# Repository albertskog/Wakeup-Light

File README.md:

#Raspberry Pi Wakeup-Light
This is the readme.

#MQTT API
###lights/r
A single integer value from 0 to 999 posted (as string) on this topic sets the red pulse width accordingly.

###lights/g
A single integer value from 0 to 999 posted (as string) on this topic sets the green pulse width accordingly.

###lights/b
A single integer value from 0 to 999 posted (as string) on this topic sets the blue pulse width accordingly.

###lights/rgb
A JSON object published on this topic sets all the colors at once. The key "fadeTimeMs" is optional and makes a fade from the previously set color to the new one in the time specified. Syntax:

	{
		"red":        500, 
		"green":      300, 
		"blue":       100,
		"fadeTimeMs": 1000
	}

###wakeup/state
A JSON object published on this topic sets the current state of the wakeup light sequence. Stopping the sequence while running will keep the last light setting. 

States may be one of the following:

- "start" or 1
- "stop" or 0

The parameter "wakeupTime" may optionally be passed to set the duration of the wakeup sequence.

Syntax:

	{
		"state": "start",
		"wakeupTimeMinutes": 30
	}

Alternative:

	{
		"state": 1
	}

###wakeup/time
A JSON object published on this topic sets the time it takes to perform the fading sequence. Syntax:

	{
		"wakeupTimeMinutes": 25
	}

###wakeup/alarm
A JSON object published on this topic sets the time for the wakeup sequence to start. This is an alternative to starting the sequence manually. The content will be parsed into a cronjob so comma separation can be used to add several values and "*" means "every". Syntax:

	{
		"hour":   "7", 
		"minute": "30", 
		"day": 	  "1, 2, 3, 4, 5",
		"month":  "*"
	}

#Installing

###Basics

	sudo apt-get install git screen man python-pip python-dev

###Mosquitto MQTT Broker
Get the latest version from their repository
([http://mosquitto.org/2013/01/mosquitto-debian-repository/](http://mosquitto.org/2013/01/mosquitto-debian-repository/))

```
wget http://repo.mosquitto.org/debian/mosquitto-repo.gpg.key
sudo apt-key add mosquitto-repo.gpg.key
cd /etc/apt/sources.list.d/
sudo wget http://repo.mosquitto.org/debian/mosquitto-stable.list
sudo apt-get update
sudo apt-get install mosquitto
```

###Paho MQTT Python library
([http://mosquitto.org/documentation/python/](http://mosquitto.org/documentation/python/))

	sudo pip install paho-mqtt

###Raspberry GPIO

	sudo pip install RPIO

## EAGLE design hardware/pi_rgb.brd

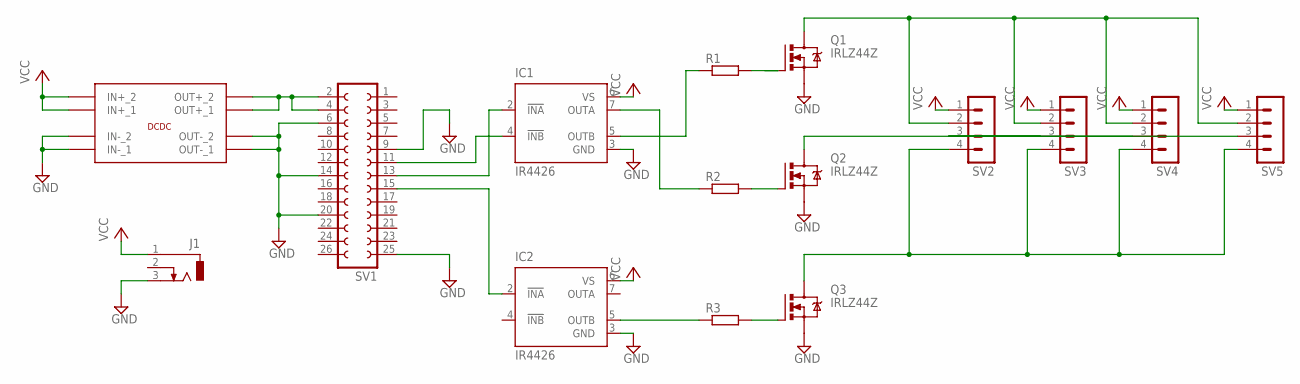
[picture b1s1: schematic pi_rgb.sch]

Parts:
5V: DCDC
IC1, IC2: IR4426; DIL08
J1: DCJ0303
Q1, Q2, Q3: IRLZ44Z; TO220BV
R1, R2, R3: R-EU_0204_5; 0204/5
SV1: FE13-2
SV2, SV3, SV4, SV5: MA04-1

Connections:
GND: 5V.IN-_1, 5V.IN-_2, 5V.OUT-_1, 5V.OUT-_2, IC1.3 (GND), IC2.3 (GND), J1.3, Q1.S, Q2.S, Q3.S, SV1.6, SV1.9, SV1.14, SV1.20, SV1.25
unnamed: IC1.4 (!INB), SV1.11
unnamed: IC1.2 (!INA), SV1.13
unnamed: IC2.2 (!INA), SV1.15
unnamed: Q2.G, R2.2
unnamed: Q3.G, R3.2
unnamed: IC2.5 (OUTB), R3.1
unnamed: Q2.D, SV2.3, SV3.3, SV4.3, SV5.3
unnamed: Q3.D, SV2.4, SV3.4, SV4.4, SV5.4
unnamed: 5V.OUT+2 (OUT+_1), 5V.OUT+_1 (OUT+_2), SV1.2, SV1.4
unnamed: Q1.G, R1.2
unnamed: Q1.D, SV2.2, SV3.2, SV4.2, SV5.2
unnamed: IC1.7 (OUTA), R2.1
unnamed: IC1.5 (OUTB), R1.1
VCC: 5V.IN+_1, 5V.IN+_2, IC1.6 (VS), IC2.6 (VS), J1.1, SV2.1, SV3.1, SV4.1, SV5.1

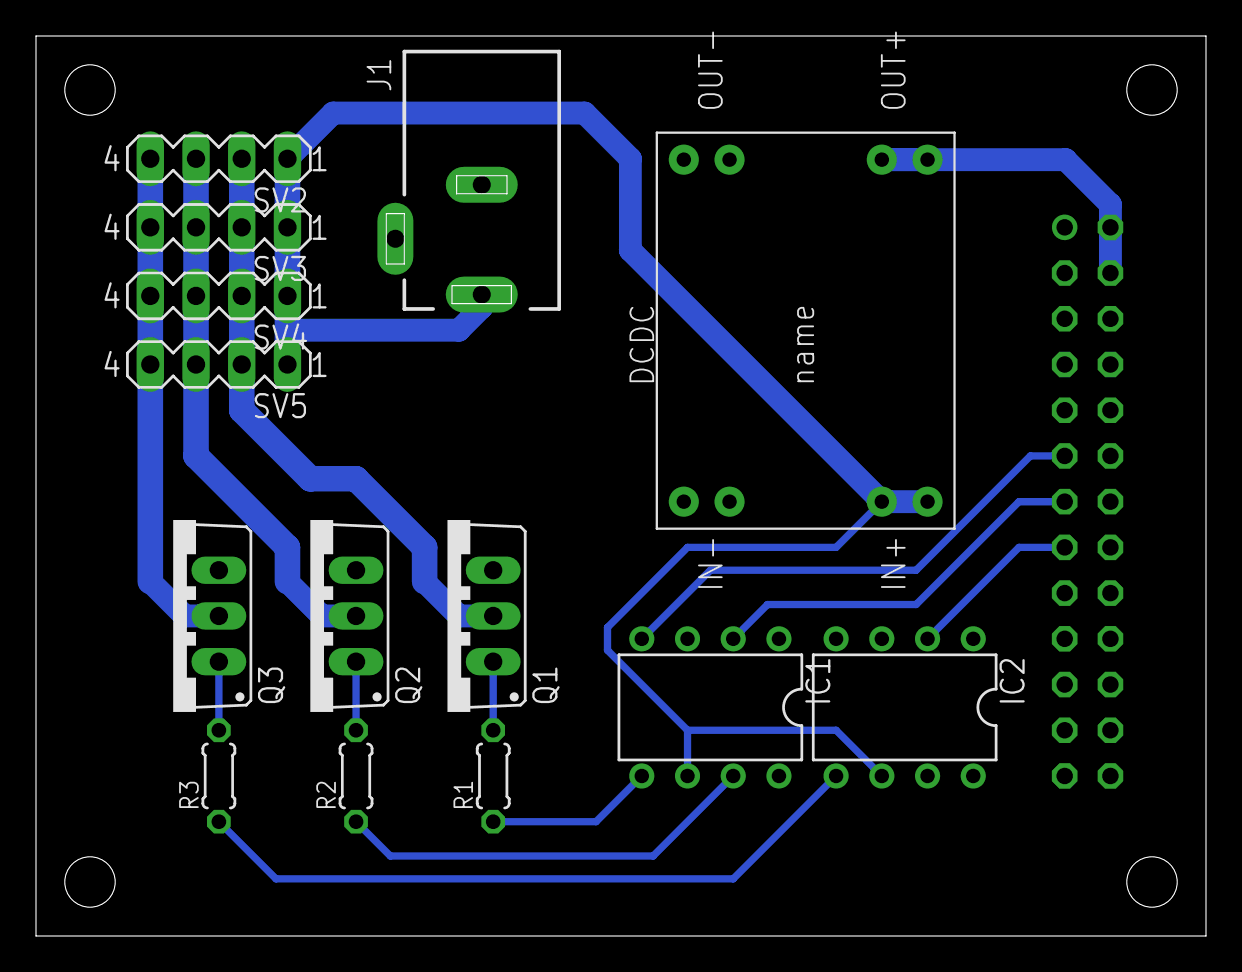
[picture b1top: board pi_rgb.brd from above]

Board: 2 copper layers, 65.0 x 50.0 mm, 15 parts (1 on the bottom side), 15 nets.

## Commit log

2014-11-16 First commit. Basic installation.
2014-11-23 Updated fade time for real test
2014-11-24 quick fixed exit crash
2014-11-25 Added simple JSON api to set all three colors at once
2014-11-26 Inital project setup
2014-11-26 moved files into /app
2014-11-26 moved .idea
2014-11-26 Updated and created a new .gitignore
2014-11-26 Updated .gitignore
2014-11-28 Started expanding wakeup API
2014-12-09 refactoring - moving out classes from rgbControl.py
2014-12-09 More refactoring. Moved wakeup.py into rgb.py. Also added functionality to start and stop wakeup sequence through the proper API call.
2014-12-09 forgot to remove rgbControl.py, moved to wakeup-light.py
2015-01-16 added installation info to readme
2015-01-18 added small script to start the wakeup sequence. good to put in cronjob
2015-01-25 Added wakeup fade time to API
2015-01-25 Changed hardcoded IPs to localhost and fixed time calculations for wakeup time
2015-01-25 Whitespace...
2015-01-26 First test version of more dynamic fader
2015-02-01 Added PCB layout
2015-02-01 added the right files...
2015-02-07 Moved all RPIO functionallity into API wrapper pwm.py
2015-02-08 Fixed indenting, it works
2015-02-08 Fade now goes to max on all colors
2015-09-07 added simple script for setting rgb levels from the command line
2015-09-14 Added some debug output and put a delay in the main loop to see if it affects issue with crashing
2015-09-14 Changed pinout
2015-09-14 added *.pyc to .gitignore
2015-09-20 Added periodic task class as submodule
2015-09-20 Updated periodic task filename
2015-09-20 Added script to stop fade, useful for debugging.
2015-09-20 Started using periodic task to do fade. Changed some formatting to match PEP8.
